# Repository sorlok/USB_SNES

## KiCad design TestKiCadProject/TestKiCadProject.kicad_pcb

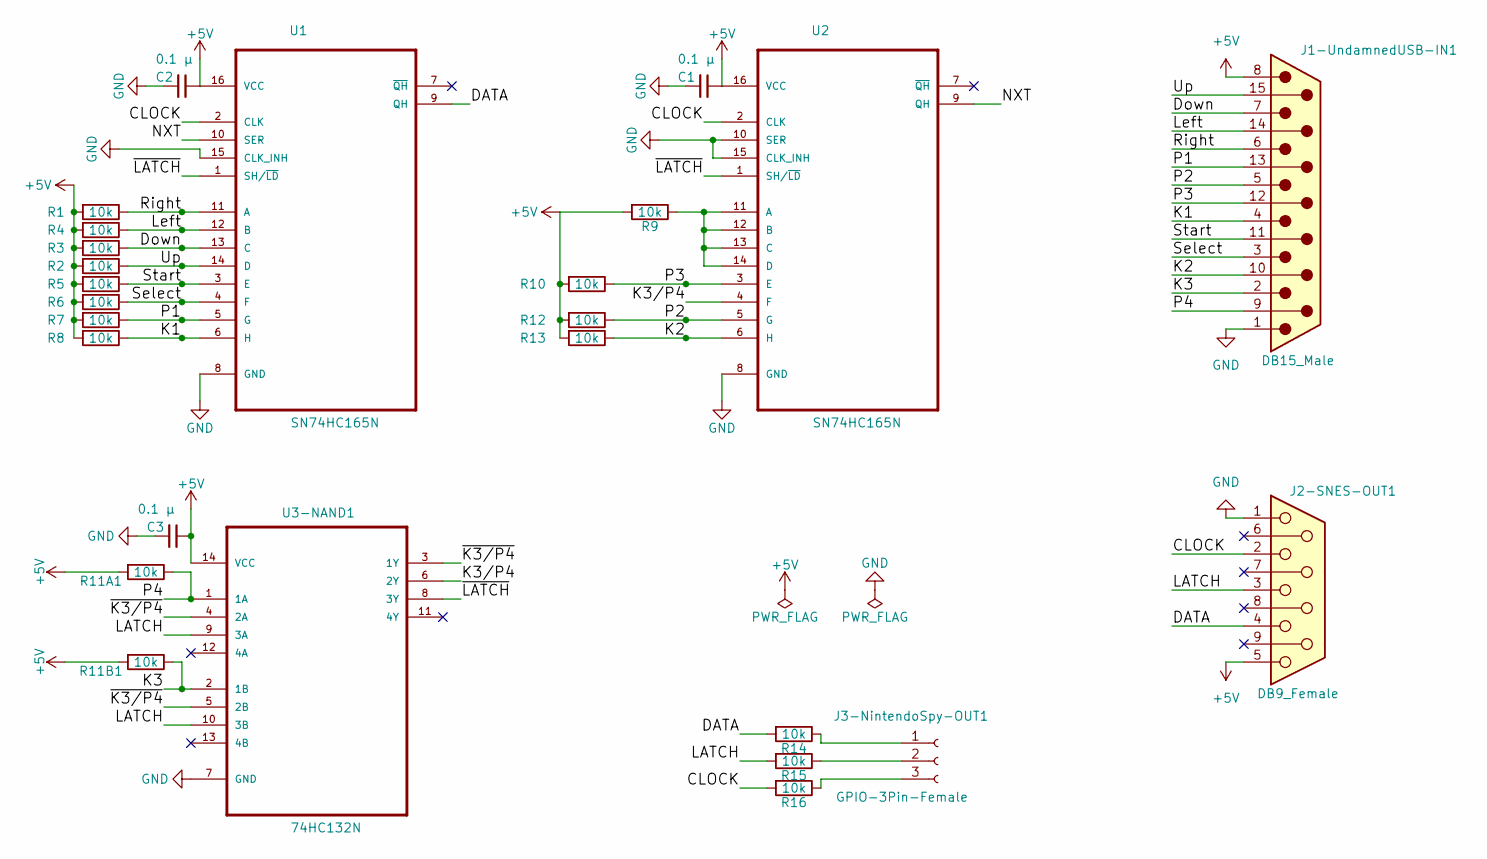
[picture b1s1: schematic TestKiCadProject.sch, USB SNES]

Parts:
C1, C2, C3: 0.1 μ; C_0603
J1-UndamnedUSB-IN1: DB15_Male; DSUB-15_Male_EdgeMount_Pitch2.77mm
J2-SNES-OUT1: DB9_Female; DSUB-9_Male_EdgeMount_Pitch2.77mm
J3-NintendoSpy-OUT1: GPIO-3Pin-Female; Pin_Header_Angled_1x03_Pitch2.54mm
R1, R2, R3, R4, R5, R6, R7, R8, R9, R10, R11A1, R11B1, R12, R13, R14, R15, R16: 10k; R_0603
U1, U2: SN74HC165N; SO-16-N
U3-NAND1: 74HC132N; SOIC-14_N

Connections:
+5V: C1.1, C2.1, C3.1, J1-UndamnedUSB-IN1.8, J2-SNES-OUT1.5, R1.2, R2.2, R3.2, R4.2, R5.2, R6.2, R7.2, R8.2, R9.2, R10.2, R11A1.2, R11B1.2, R12.2, R13.2, U1.16 (VCC), U2.16 (VCC), U3-NAND1.14 (VCC)
/CLOCK: J2-SNES-OUT1.2, R16.2, U1.2 (CLK), U2.2 (CLK)
/DATA: J2-SNES-OUT1.4, R14.2, U1.9 (QH)
/Down: J1-UndamnedUSB-IN1.7, R3.1, U1.13 (C)
/K1: J1-UndamnedUSB-IN1.4, R8.1, U1.6 (H)
/K2: J1-UndamnedUSB-IN1.10, R13.1, U2.6 (H)
/K3: J1-UndamnedUSB-IN1.2, R11B1.1, U3-NAND1.2 (1B)
/K3/P4: U2.4 (F), U3-NAND1.6 (2Y)
/LATCH: J2-SNES-OUT1.3, R15.2, U3-NAND1.9 (3A), U3-NAND1.10 (3B)
/Left: J1-UndamnedUSB-IN1.14, R4.1, U1.12 (B)
/NXT: U1.10 (SER), U2.9 (QH)
/P1: J1-UndamnedUSB-IN1.13, R7.1, U1.5 (G)
/P2: J1-UndamnedUSB-IN1.5, R12.1, U2.5 (G)
/P3: J1-UndamnedUSB-IN1.12, R10.1, U2.3 (E)
/P4: J1-UndamnedUSB-IN1.9, R11A1.1, U3-NAND1.1 (1A)
/Right: J1-UndamnedUSB-IN1.6, R1.1, U1.11 (A)
/Select: J1-UndamnedUSB-IN1.3, R6.1, U1.4 (F)
/Start: J1-UndamnedUSB-IN1.11 (P111), R5.1, U1.3 (E)
/Up: J1-UndamnedUSB-IN1.15, R2.1, U1.14 (D)
/~K3/P4: U3-NAND1.3 (1Y), U3-NAND1.4 (2A), U3-NAND1.5 (2B)
/~LATCH: U1.1 (SH/~LD), U2.1 (SH/~LD), U3-NAND1.8 (3Y)
GND: C1.2, C2.2, C3.2, J1-UndamnedUSB-IN1.1, J2-SNES-OUT1.1, U1.8 (GND), U1.15 (CLK_INH), U2.8 (GND), U2.10 (SER), U2.15 (CLK_INH), U3-NAND1.7 (GND)
unnamed: J3-NintendoSpy-OUT1.1, R14.1
unnamed: J3-NintendoSpy-OUT1.2, R15.1
unnamed: J3-NintendoSpy-OUT1.3, R16.1
unnamed: R9.1, U2.11 (A), U2.12 (B), U2.13 (C), U2.14 (D)

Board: 2 copper layers, 26 parts (0 on the bottom side), 26 nets, no tracks yet.

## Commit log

2018-07-10 Initial plans: circuit diagram is done
2018-07-12 Add additional footprints/layouts as a local folder
2018-07-12 Default footprint
2018-07-12 Some footprint associations
